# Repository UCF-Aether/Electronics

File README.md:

# Aether Electronics
The schematic is viewable as a PDF in the latest release. To view in KiCad, make sure you have KiCad 6 installed, and simply clone the repo and open `aether.kicad_pro`.

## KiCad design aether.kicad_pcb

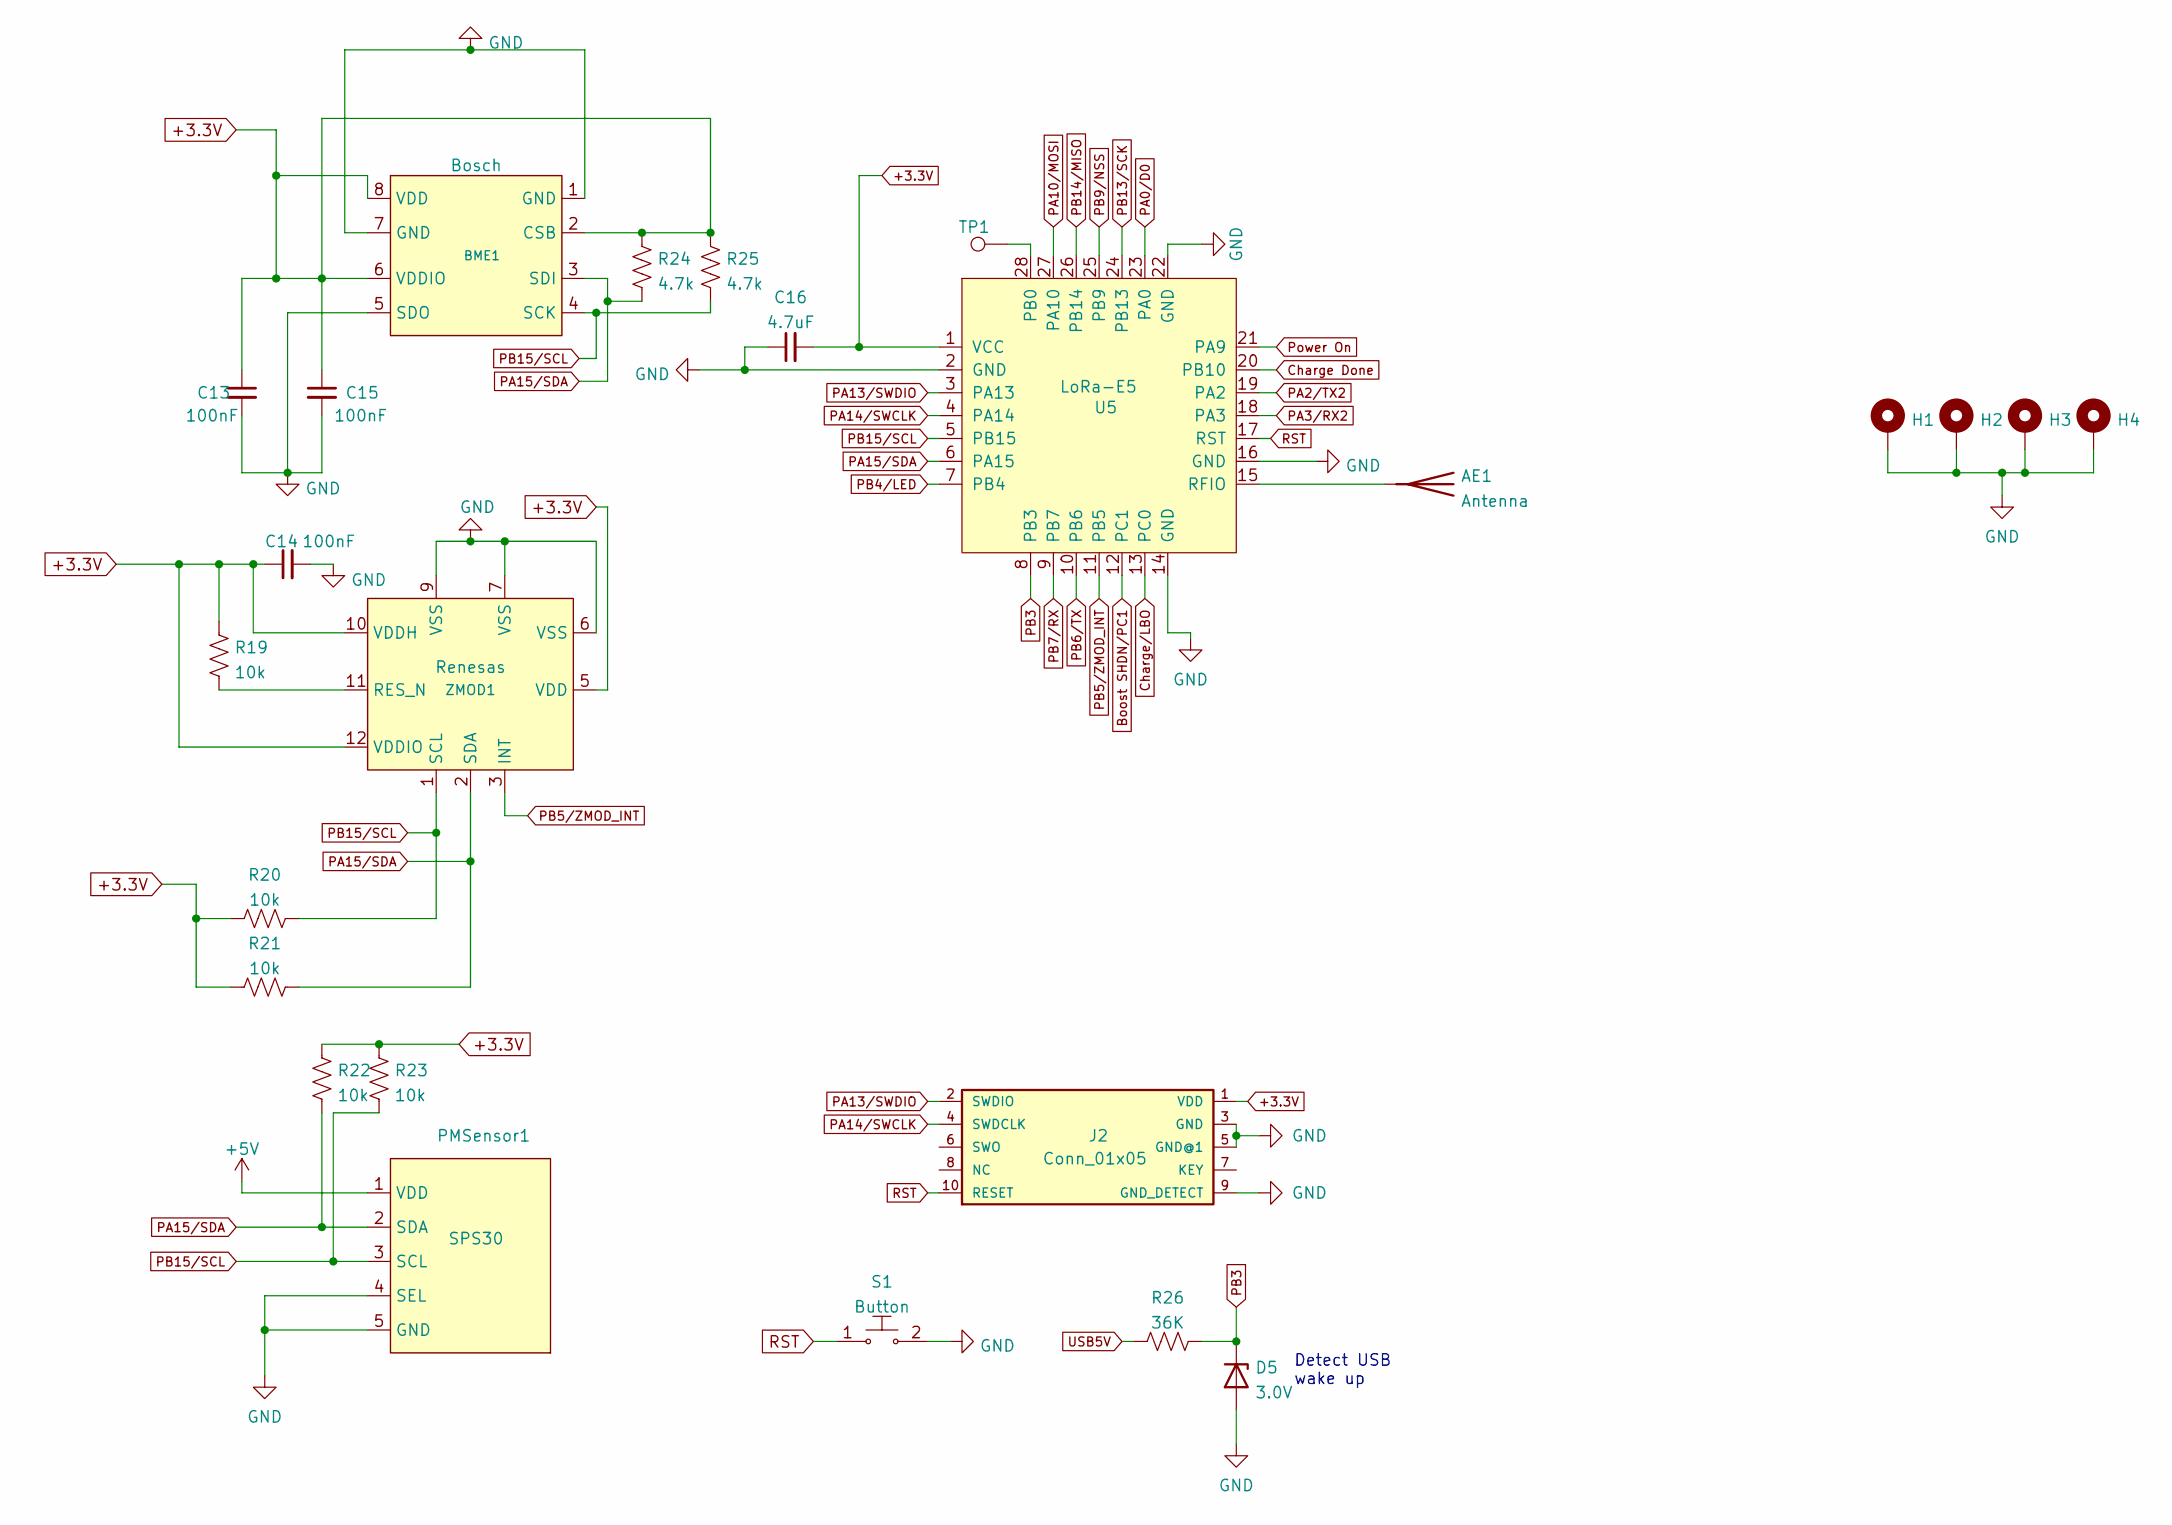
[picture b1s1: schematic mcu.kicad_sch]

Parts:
AE1: Antenna; SMA_Amphenol_132134_Vertical
BME1: Bosch; Bosch_LGA-8_3x3mm_P0.8mm_ClockwisePinNumbering
C13, C14, C15: 100nF; C_0805_2012Metric_Pad1.18x1.45mm_HandSolder
C16: 4.7uF; C_0805_2012Metric_Pad1.18x1.45mm_HandSolder
D5: 3.0V; D_0805_2012Metric_Pad1.15x1.40mm_HandSolder
H1, H2, H3, H4: MountingHole; MountingHole_2.2mm_M2_ISO14580_Pad_TopBottom
J2: Conn_01x05; 2X10_BOXHEADER
PMSensor1: SPS30; JST_EH_B5B-EH-A_1x05_P2.50mm_Vertical
R19, R20, R21, R22, R23: 10k; R_0805_2012Metric_Pad1.20x1.40mm_HandSolder
R24, R25: 4.7k; R_0805_2012Metric_Pad1.20x1.40mm_HandSolder
R26: 36K; R_0805_2012Metric_Pad1.20x1.40mm_HandSolder
S1: Button; SW_Push_1P1T_NO_6x6mm_H9.5mm; MPN GPTS203211B; Digi-Key_PN CW181-ND
TP1: TestPoint; TestPoint_Keystone_5005-5009_Compact
U5: LoRa-E5
ZMOD1: Renesas; ZMOD4510

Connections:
+3.3V: BME1.2 (CSB), BME1.6 (VDDIO), BME1.8 (VDD), C13.1, C14.1, C15.1, C16.2, J2.1 (VDD), R19.1, R20.1, R21.1, R22.1, R23.1, R24.1, R25.1, U5.1 (VCC), ZMOD1.5 (VDD), ZMOD1.10 (VDDH), ZMOD1.12 (VDDIO); also elsewhere on the board
+5V: PMSensor1.1 (VDD); also elsewhere on the board
Boost SHDN/PC1: U5.12 (PC1); also elsewhere on the board
Charge Done: U5.20 (PB10); also elsewhere on the board
Charge/LBO: U5.13 (PC0); also elsewhere on the board
GND: BME1.1 (GND), BME1.5 (SDO), BME1.7 (GND), C13.2, C14.2, C15.2, C16.1, D5.2 (A), H1.1, H2.1, H3.1, H4.1, J2.3 (GND), J2.5 (GND@1), J2.9 (GND_DETECT), PMSensor1.4 (SEL), PMSensor1.5 (GND), S1.2, U5.2 (GND), U5.14 (GND), U5.16 (GND), U5.22 (GND), ZMOD1.6 (VSS), ZMOD1.7 (VSS), ZMOD1.9 (VSS); also elsewhere on the board
unnamed: AE1.1 (A), U5.15 (RFIO)
unnamed: R19.2, ZMOD1.11 (RES_N)
unnamed: TP1.1, U5.28 (PB0)
PA0/D0: U5.23 (PA0)
PA2/TX2: U5.19 (PA2)
PA3/RX2: U5.18 (PA3)
PA10/MOSI: U5.27 (PA10)
PA13/SWDIO: J2.2 (SWDIO), U5.3 (PA13)
PA14/SWCLK: J2.4 (SWDCLK), U5.4 (PA14)
PA15/SDA: BME1.3 (SDI), PMSensor1.2 (SDA), R21.2, R22.2, R24.2, U5.6 (PA15), ZMOD1.2 (SDA)
PB3: D5.1 (K), R26.2, U5.8 (PB3)
PB4/LED: U5.7 (PB4); also elsewhere on the board
PB5/ZMOD_INT: U5.11 (PB5), ZMOD1.3 (INT)
PB6/TX: U5.10 (PB6); also elsewhere on the board
PB7/RX: U5.9 (PB7); also elsewhere on the board
PB9/NSS: U5.25 (PB9)
PB13/SCK: U5.24 (PB13~)
PB14/MISO: U5.26 (PB14)
PB15/SCL: BME1.4 (SCK), PMSensor1.3 (SCL), R20.2, R23.2, R25.2, U5.5 (PB15), ZMOD1.1 (SCL)
Power On: U5.21 (PA9); also elsewhere on the board
RST: J2.10 (RESET), S1.1, U5.17 (RST); also elsewhere on the board
USB5V: R26.1; also elsewhere on the board

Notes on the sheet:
Detect USB wake up

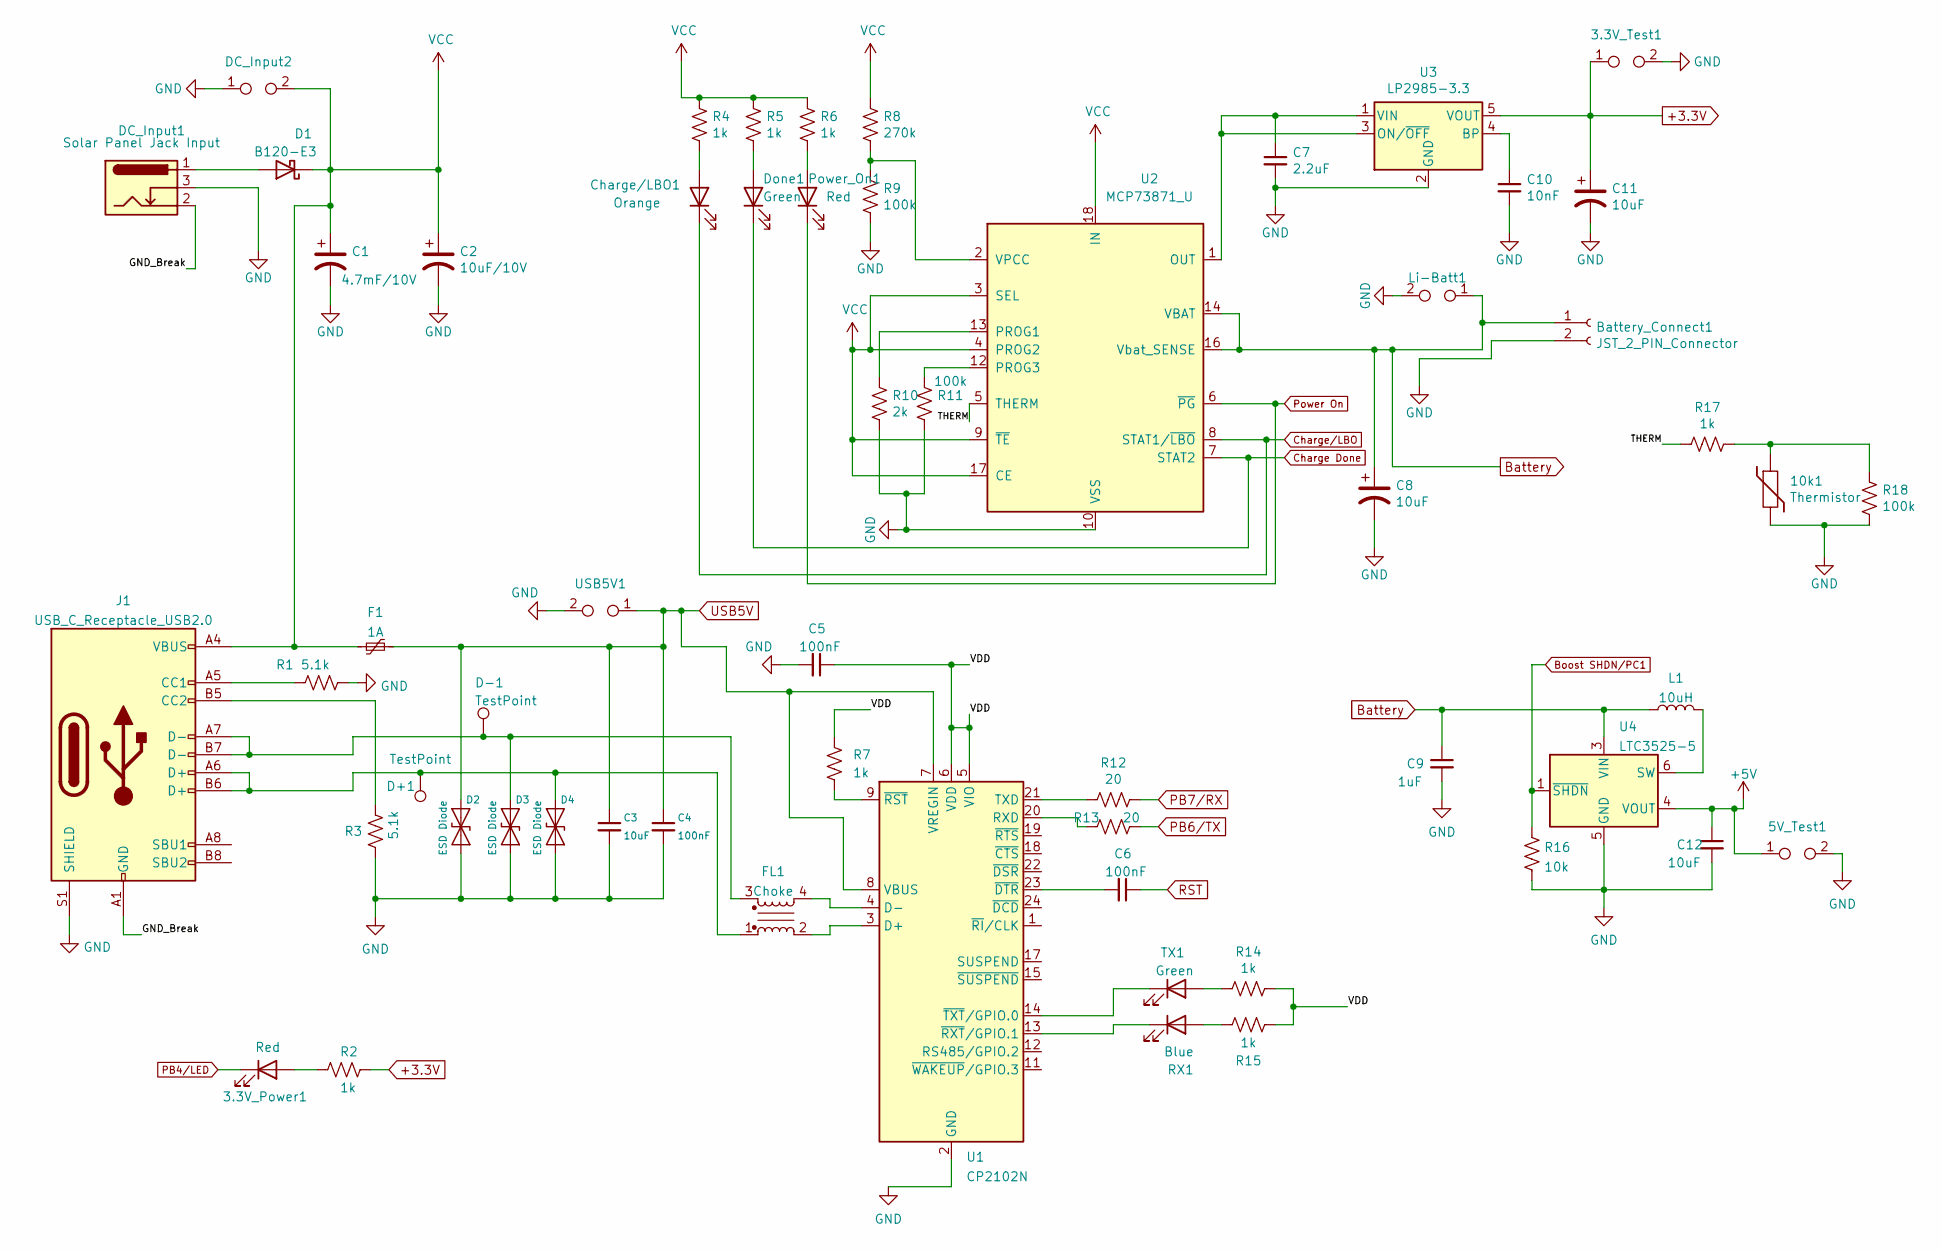
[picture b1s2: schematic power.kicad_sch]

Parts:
3.3V_Power1: Red; LED_0805_2012Metric_Pad1.15x1.40mm_HandSolder
3.3V_Test1, 5V_Test1: TestPoint; TestPoint_2Pads_Pitch2.54mm_Drill0.8mm
10k1: Thermistor; TerminalBlock_Altech_AK300-2_P5.00mm
Battery_Connect1: JST_2_PIN_Connector; JST_PH_B2B-PH-SM4-TB_1x02-1MP_P2.00mm_Vertical
C1: 4.7mF/10V; CP_Radial_D13.0mm_P5.00mm
C2: 10uF/10V; C_0805_2012Metric_Pad1.18x1.45mm_HandSolder
C3, C8, C11, C12: 10uF; C_0805_2012Metric_Pad1.18x1.45mm_HandSolder
C4, C5, C6: 100nF; C_0805_2012Metric_Pad1.18x1.45mm_HandSolder
C7: 2.2uF; C_0805_2012Metric_Pad1.18x1.45mm_HandSolder
C9: 1uF; C_0805_2012Metric_Pad1.18x1.45mm_HandSolder
C10: 10nF; C_0805_2012Metric_Pad1.18x1.45mm_HandSolder
Charge/LBO1: Orange; LED_0805_2012Metric_Pad1.15x1.40mm_HandSolder
D1: B120-E3; D_SMA
D2, D3, D4: ESD Diode; D_0402_1005Metric_Pad0.77x0.64mm_HandSolder
D+1: TestPoint; TestPoint_Keystone_5000-5004_Miniature
D-1: TestPoint; TestPoint_Keystone_5000-5004_Miniature
DC_Input1: Solar Panel Jack Input; BarrelJack_Horizontal
DC_Input2: TestPoint; TestPoint_2Pads_Pitch2.54mm_Drill0.8mm
Done1: Green; LED_0805_2012Metric_Pad1.15x1.40mm_HandSolder
F1: 1A; Fuse_0805_2012Metric_Pad1.15x1.40mm_HandSolder
FL1: Choke; L_CommonModeChoke_Coilcraft_0805USB
J1: USB_C_Receptacle_USB2.0; USB_C_Receptacle_XKB_U262-16XN-4BVC11
L1: 10uH; L_0805_2012Metric_Pad1.15x1.40mm_HandSolder
Li-Batt1: TestPoint; TestPoint_2Pads_Pitch2.54mm_Drill0.8mm
Power_On1: Red; LED_0805_2012Metric_Pad1.15x1.40mm_HandSolder
R1, R3: 5.1k; R_0805_2012Metric_Pad1.20x1.40mm_HandSolder
R2, R4, R5, R6, R7, R14, R15, R17: 1k; R_0805_2012Metric_Pad1.20x1.40mm_HandSolder
R8: 270k; R_0805_2012Metric_Pad1.20x1.40mm_HandSolder
R9, R11, R18: 100k; R_0805_2012Metric_Pad1.20x1.40mm_HandSolder
R10: 2k; R_0805_2012Metric_Pad1.20x1.40mm_HandSolder
R12, R13: 20; R_0805_2012Metric_Pad1.20x1.40mm_HandSolder
R16: 10k; R_0805_2012Metric_Pad1.20x1.40mm_HandSolder
RX1: Blue; LED_0805_2012Metric_Pad1.15x1.40mm_HandSolder
TX1: Green; LED_0805_2012Metric_Pad1.15x1.40mm_HandSolder
U1: CP2102N; QFN-24-1EP_4x4mm_P0.5mm_EP2.6x2.6mm
U2: MCP73871_U; QFN-20-1EP_4x4mm_P0.5mm_EP2.5x2.5mm
U3: LP2985-3.3; SOT-23-5
U4: LTC3525-5; SOT-363_SC-70-6
USB5V1: TestPoint; TestPoint_2Pads_Pitch2.54mm_Drill0.8mm

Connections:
+3.3V: 3.3V_Test1.1, C11.1, R2.2, U3.5 (VOUT); also elsewhere on the board
+5V: 5V_Test1.1, C12.1, U4.4 (VOUT); also elsewhere on the board
/Power/GND_Break: DC_Input1.2, J1.A1 (GND), J1.A12 (GND), J1.B1 (GND), J1.B12 (GND)
/Power/THERM: R17.2, U2.5 (THERM)
/Power/VDD: C5.1, R7.2, R14.1, R15.1, U1.5 (VIO), U1.6 (VDD)
Battery: Battery_Connect1.1, C8.1, C9.1, L1.1, Li-Batt1.1, U2.14 (VBAT), U2.15 (VBAT), U2.16 (Vbat_SENSE), U4.3 (VIN)
Boost SHDN/PC1: R16.1, U4.1 (~SHDN); also elsewhere on the board
Charge Done: Done1.1 (K), U2.7 (STAT2); also elsewhere on the board
Charge/LBO: Charge/LBO1.1 (K), U2.8 (STAT1/~LBO); also elsewhere on the board
GND: 3.3V_Test1.2, 5V_Test1.2, 10k1.2, Battery_Connect1.2, C1.2, C2.2, C3.2, C4.2, C5.2, C7.2, C8.2, C9.2, C10.2, C11.2, C12.2, D2.2 (A2), D3.2 (A2), D4.2 (A2), DC_Input1.3, DC_Input2.1, J1.S1 (SHIELD), Li-Batt1.2, R1.1, R3.1, R9.1, R10.1, R11.1, R16.2, R18.1, U1.2 (GND), U1.25 (GND), U2.10 (VSS), U2.11 (VSS), U2.21 (VSS), U3.2 (GND), U4.2 (GND), U4.5 (GND), USB5V1.2; also elsewhere on the board
unnamed: 3.3V_Power1.2 (A), R2.1
unnamed: 10k1.1, R17.1, R18.2
unnamed: C6.2, U1.23 (~DTR)
unnamed: C7.1, U2.1 (OUT), U2.20 (OUT), U3.1 (VIN), U3.3 (ON/~OFF)
unnamed: C10.1, U3.4 (BP)
unnamed: Charge/LBO1.2 (A), R4.1
unnamed: D1.2 (A), DC_Input1.1
unnamed: D4.1 (A1), D+1.1, FL1.1, J1.A6 (D+), J1.B6 (D+)
unnamed: D3.1 (A1), D-1.1, FL1.3, J1.A7 (D-), J1.B7 (D-)
unnamed: Done1.2 (A), R5.1
unnamed: FL1.2, U1.3 (D+)
unnamed: FL1.4, U1.4 (D-)
unnamed: J1.A5 (CC1), R1.2
unnamed: J1.B5 (CC2), R3.2
unnamed: L1.2, U4.6 (SW)
unnamed: Power_On1.2 (A), R6.1
unnamed: R7.1, U1.9 (~RST)
unnamed: R8.1, R9.2, U2.2 (VPCC)
unnamed: R10.2, U2.13 (PROG1)
unnamed: R11.2, U2.12 (PROG3)
unnamed: R12.2, U1.21 (TXD)
unnamed: R13.2, U1.20 (RXD)
unnamed: R14.2, TX1.2 (A)
unnamed: R15.2, RX1.2 (A)
unnamed: RX1.1 (K), U1.13 (~RXT/GPIO.1)
unnamed: TX1.1 (K), U1.14 (~TXT/GPIO.0)
PB4/LED: 3.3V_Power1.1 (K); also elsewhere on the board
PB6/TX: R13.1; also elsewhere on the board
PB7/RX: R12.1; also elsewhere on the board
Power On: Power_On1.1 (K), U2.6 (~PG); also elsewhere on the board
RST: C6.1; also elsewhere on the board
USB5V: C3.1, C4.1, D2.1 (A1), F1.2, U1.7 (VREGIN), U1.8 (VBUS), USB5V1.1; also elsewhere on the board
VCC: C1.1, C2.1, D1.1 (K), DC_Input2.2, F1.1, J1.A4 (VBUS), J1.A9 (VBUS), J1.B4 (VBUS), J1.B9 (VBUS), R4.2, R5.2, R6.2, R8.2, U2.3 (SEL), U2.4 (PROG2), U2.9 (~TE), U2.17 (CE), U2.18 (IN), U2.19 (IN)

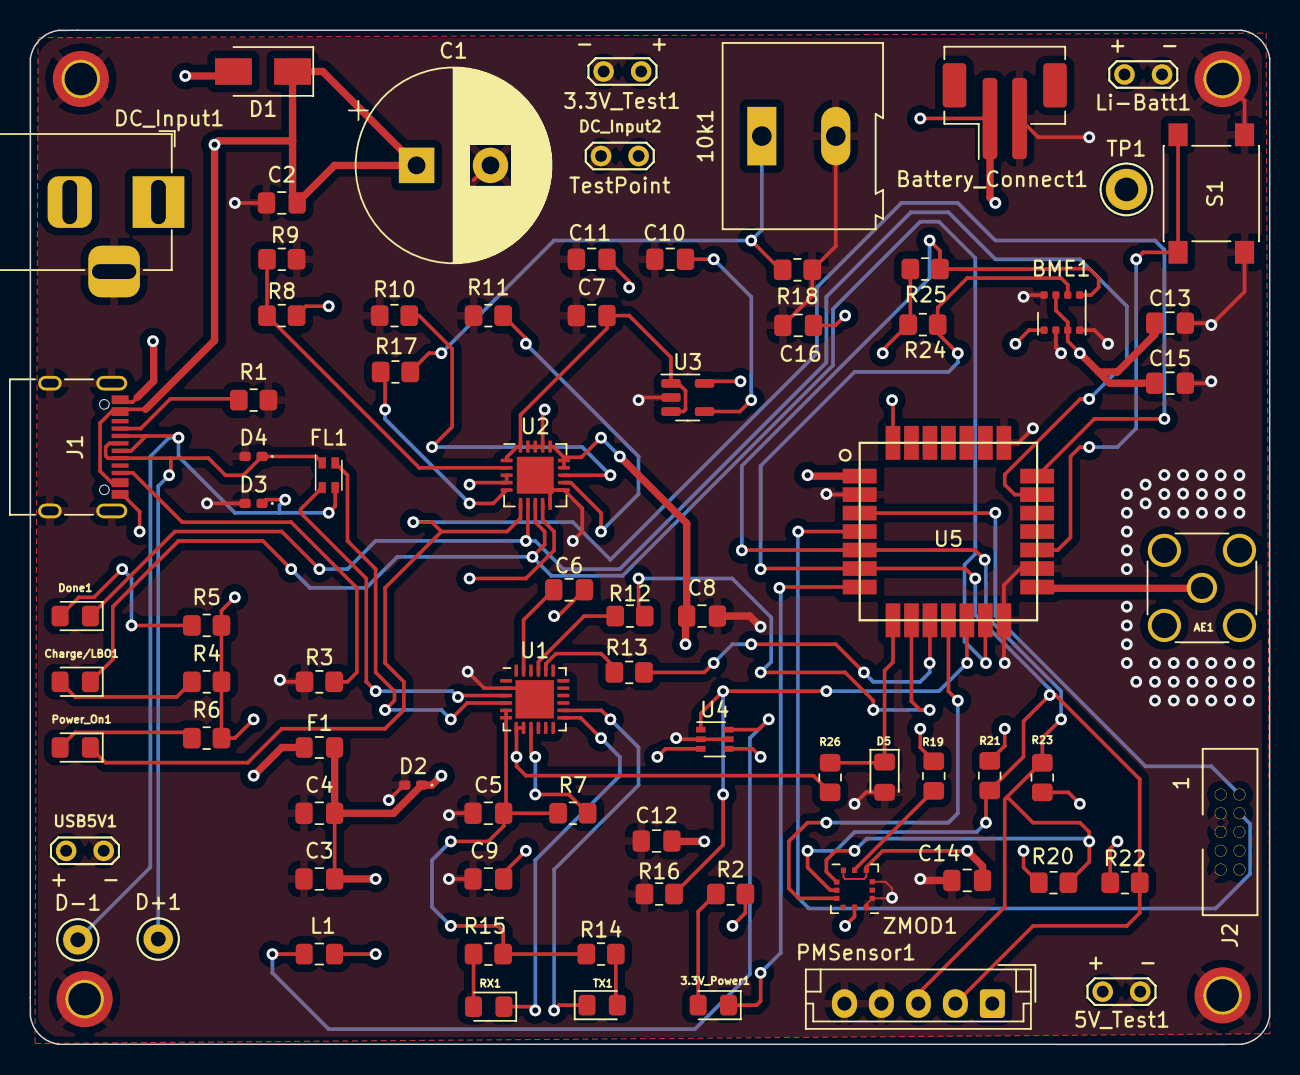
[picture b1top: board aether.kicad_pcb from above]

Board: 4 copper layers, 83.8 x 68.6 mm, 83 parts (0 on the bottom side), 52 nets.

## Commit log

2021-10-21 init: blank kicad project
2021-10-26 lib: added lora-e5
2021-10-26 docs: added how to add libraries
2021-10-27 feat: added gitignores for kicad 5.99/6.0
2021-10-27 sch: start lora module
2021-11-28 Reorganized repo & added power schematic
2021-11-28 Added Digikey library
    - Added to symbol and footprint tables
    - Using fork updated for KiCad 6
2021-11-28 Updated readme for submodule init and update
2021-11-28 Updated submodules to use https instead of ssh
    plz work
2021-11-28 Added MCU sch sheet and updated sheet layout
2021-11-30 Created Sensor Library
    - Added Bosch BME688, SPS30, ZMOD symbols to MCU schematic
2021-12-01 Connected ZMOD and Bosch Sensors
    -
2021-12-02 USB Comm Interface complete; Sensor and MCU connection complete;
    -
2021-12-04 A few schematic changes and fixes
    -
2021-12-07 -
    -
2021-12-07 USB updated. All footprints added for the most part
    -
2022-01-02 Some schematic changes. Preliminary PCB layout complete, routing not done yet
    -
2022-01-03 Generated more 3d models for pcb
    -
2022-01-14 PCB edits
    -
2022-01-18 Rearranged PCB for more efficient routing
    -
2022-01-18 PCB Routed
    -
2022-01-21 DRC runs with 0 Errors. Updates connections and footprints.
    -
2022-01-25 ZMOD Changes made
    -
2022-01-28 Edits
    -
2022-04-24 Updated Schematics
    -
2022-04-25 Final Schematic
    -
